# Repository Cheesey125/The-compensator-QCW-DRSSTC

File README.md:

I am dead set on creating the best QCW DRSSTC that I reasonably can (So, not the size of a building). So, after taking some inspiration from LTT (the name), I went to work.

Here's the plan:

A FPGA or similar based DRSSTC driver

All ultrafast comparators based on the TLV3604DCKR comparator

In Loneocean's QCW DRSSTC, the protection for the async buck converter is not isolated, meaning that the DRSSTC driver isn't isolated from mains (As far as I and some others could tell). So, for that (and for the UVLO for the isolated power supplies), I chose the SFH617A-1 to isolate at a relatively fast speed (as far as optocouplers go)

Gate Drivers - UCC5390ECQDWVRQ1

Modular Primary Capacitors
      -One based on the unobtanium cylindrical mica capacitor
      -One based on some large C0G SMD ceramic capacitors
      -One based on the sketchy Ebay ceramic doorknobs
      -One based on one of the traditional film MMCs
      
Modular Primary Coils
      -Due to the different values that are unavoidable in the modular primary capacitors, separate primary coils would be required to maintain secondary and primary resonance.
      
Inverter - Triple full bridge using FGH75T65SQD-F155 IGBTs

Buck Converter - Either three parallel FGH75T65SQD-F155 IGBTs or an IGBT brick.

Cooling - TBD, may do water cooling :troll:

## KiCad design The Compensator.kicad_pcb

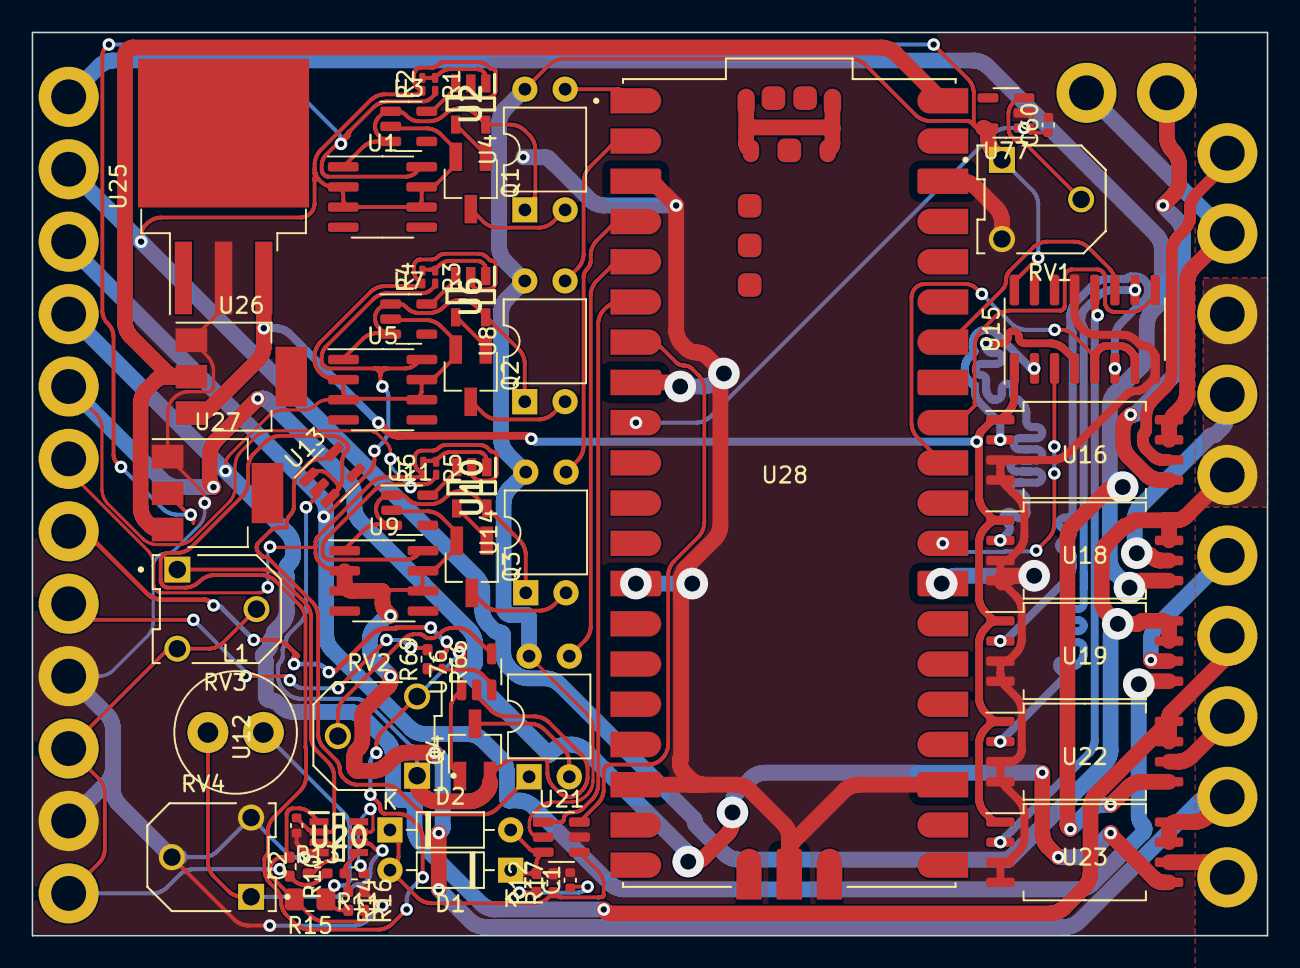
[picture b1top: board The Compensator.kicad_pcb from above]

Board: 2 copper layers, 78.0 x 57.0 mm, 58 parts (0 on the bottom side), 62 nets.

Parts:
C1, C60: CL05A104KA5NNNC; C_0402_1005Metric
C2: CGA2B3X7R1H473K050BB; C_0402_1005Metric
D1, D2: 1N4148; D_DO-35_SOD27_P7.62mm_Horizontal
L1: RLB0812-473KL; L_Radial_D7.5mm_P3.50mm_Fastron_07P
Q1, Q2, Q3, Q4: Q_NPN_BEC; SC-59_Handsoldering
R1, R3, R5: RMCF0201FT10K0; R_0201_0603Metric_Pad0.64x0.40mm_HandSolder
R2, R4, R6: RC0201FR-071KL; R_0201_0603Metric_Pad0.64x0.40mm_HandSolder
R10, R11, R12, R13, R14, R17: CR0402-FX-1001GLF; R_0402_1005Metric_Pad0.72x0.64mm_HandSolder
R15: CRCW08056R80JNEA; R_0805_2012Metric_Pad1.20x1.40mm_HandSolder
R16: CRCW040247K0JNEDC; R_0402_1005Metric_Pad0.72x0.64mm_HandSolder
R66: RC0201FR-071ML; R_0201_0603Metric_Pad0.64x0.40mm_HandSolder
R69: RC0402FR-074K99L; R_0402_1005Metric_Pad0.72x0.64mm_HandSolder
RV1, RV2, RV3, RV4: 3306F-1-103; TRIM_3306F-1-103
U1, U5, U9: MC78L05ACPRPG; SOIC-8_3.9x4.9mm_P1.27mm
U2, U6, U10: LMV331W5-7; SOT95P285X140-5N
U3, U7, U11, U13: MIC5504-1.8YM5; SOT-23-5
U4, U8, U12, U14: SFH617A-1; DIP-4_W7.62mm
U15: MC14504BDR2G; SOIC-16_3.9x9.9mm_P1.27mm
U16, U18, U19, U22, U23: UCC5390ECQDWVRQ1; SOIC-8_7.5x5.85mm_P1.27mm
U20: LM2904BIDDFR; SOT65P280X110-8N
U21: TLV3604DCKR; SOT-23-6
U25: UA7815CKTTR; TO-263-3_TabPin4
U26: NCP1117LPST50T3G; SOT-223
U27: LM1117IMP-3.3/NOPB; SOT-223
U28: SC0915; MODULE_SC0915
U76, U77: TLV3604DCKR; SOT-23-5

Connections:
+1V0: U12.1, U13.5 (VOUT)
+3.3V: RV1.1, U4.4, U8.4, U12.4, U14.4, U15.16 (VDD), U21.2 (V-), U27.2 (VO), U77.5 (V+)
+5V: U26.2 (VO), U27.3 (VI), U28.40 (VBUS)
+5VP: RV2.3, U13.1 (VIN), U13.3 (EN), U76.5 (V+)
+15V: U15.1 (VCC), U16.1 (VCC1), U18.1 (VCC1), U19.1 (VCC1), U22.1 (VCC1), U23.1 (VCC1), U25.3 (OUT), U26.3 (VI)
+24VA: R1.2, U1.8 (IN), U18.5 (VCC2), U22.5 (VCC2)
+24VB: R3.2, U5.8 (IN), U19.5 (VCC2)
+24VC: R5.2, U9.8 (IN), U23.5 (VCC2)
GND: C1.2, C2.1, C60.2, R16.1, R17.2, RV1.3, RV4.2, RV4.3, U15.8 (VSS), U15.13 (MODE), U16.3 (IN-), U16.4 (GND1), U18.3 (IN-), U18.4 (GND1), U19.3 (IN-), U19.4 (GND1), U20.4 (V-), U21.5 (V+), U22.3 (IN-), U22.4 (GND1), U23.3 (IN-), U23.4 (GND1), U25.2 (GND), U26.1 (GND), U27.1 (GND), U28.3 (GND), U28.8 (GND), U28.13 (GND), U28.18 (GND), U28.23 (GND), U28.28 (GND), U28.38 (GND), U28.D2 (GND), U77.2 (V-)
GND1: Q1.2 (E), R2.1, U1.2 (GND), U1.3 (GND), U1.6 (GND), U1.7 (GND), U2.2 (V-), U3.2 (GND), U18.7 (GND2), U18.8 (VEE2), U19.7 (GND2), U19.8 (VEE2)
GND2: Q2.2 (E), R4.1, U5.2 (GND), U5.3 (GND), U5.6 (GND), U5.7 (GND), U6.2 (V-), U7.2 (GND), U22.7 (GND2), U22.8 (VEE2)
GND3: Q3.2 (E), R6.1, U9.2 (GND), U9.3 (GND), U9.6 (GND), U9.7 (GND), U10.2 (V-), U11.2 (GND), U23.7 (GND2), U23.8 (VEE2)
GNDA: Q4.2 (E), RV2.1, U13.2 (GND), U76.2 (V-)
unnamed: C1.1, R12.1
unnamed: C2.2, RV3.1, U20.2 (-)
unnamed: C60.1, U28.9 (GP6), U77.1
unnamed: D1.2 (A), D2.1 (K), R17.1, U21.4 (-)
unnamed: D1.1 (K), D2.2 (A), R12.2, U21.3 (+)
unnamed: L1.1, RV4.1, U20.6 (-)
unnamed: L1.2, R14.2, R15.1
unnamed: Q1.1 (B), U2.4
unnamed: Q1.3 (C), U4.2
unnamed: Q2.1 (B), U6.4
unnamed: Q2.3 (C), U8.2
unnamed: Q3.1 (B), U10.4
unnamed: Q3.3 (C), U14.2
unnamed: Q4.1 (B), U76.1
unnamed: Q4.3 (C), U12.2
unnamed: R1.1, R2.2, U2.1 (+)
unnamed: R3.1, R4.2, U6.1 (+)
unnamed: R5.1, R6.2, U10.1 (+)
unnamed: R10.1, R15.2, R16.2, U20.1
unnamed: R10.2, R13.2, RV3.2, RV3.3
unnamed: R11.1, U20.7
unnamed: R11.2, R14.1, U20.5 (+)
unnamed: R13.1, U20.3 (+)
unnamed: R66.2, R69.1, U76.3 (+)
unnamed: RV1.2, U77.3 (+)
unnamed: RV2.2, U76.4 (-)
unnamed: U1.1 (OUT), U2.5 (V+), U3.1 (VIN), U3.3 (EN), U4.1
unnamed: U2.3 (-), U3.5 (VOUT)
unnamed: U5.1 (OUT), U6.5 (V+), U7.1 (VIN), U7.3 (EN), U8.1
unnamed: U6.3 (-), U7.5 (VOUT)
unnamed: U10.3 (-), U11.5 (VOUT)
unnamed: U9.1 (OUT), U10.5 (V+), U11.1 (VIN), U11.3 (EN), U14.1
unnamed: U12.3, U28.5 (GP3)
unnamed: U14.3, U28.4 (GP2)
unnamed: U15.2, U16.2 (IN+)
unnamed: U15.3, U28.29 (GP22)
unnamed: U15.4, U18.2 (IN+)
unnamed: U15.5, U15.7, U28.31 (GP26)
unnamed: U15.6, U19.2 (IN+)
unnamed: U15.9, U28.32 (GP27)
unnamed: U15.10, U22.2 (IN+)
unnamed: U15.11, U28.34 (GP28)
unnamed: U15.12, U23.2 (IN+)
unnamed: U16.7 (GND2), U16.8 (VEE2)
unnamed: U21.1, U28.6 (GP4)
unnamed: U21.6, U28.7 (GP5)
unnamed: U4.3, U28.1 (GP0)
unnamed: U8.3, U28.2 (GP1)
unnamed: U28.A (USB_SHIELD), U28.B (USB_SHIELD), U28.C (USB_SHIELD), U28.D (USB_SHIELD)
